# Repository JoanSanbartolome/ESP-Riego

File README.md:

# ESP-Riego

Controlador inalámbrico de riego por goteo basado en ESP32 e integrado en Home Assistant mediante ESPHome.

Este repositorio contiene el rediseño (v2) de la PCB desarrollada en el Trabajo Fin de Grado de Joan San Bartolomé Ferri. El proyecto original del TFG no se modifica: se importa como referencia y la v2 se diseña desde cero a partir de su análisis.

## Estado

| Fase | Estado |
|---|---|
| 0. Análisis, especificaciones y plan | ✅ |
| 1. Importación de la v1 a KiCad 10 | ⏳ |
| 2. Arquitectura y componentes | — |
| 3. Esquema v2 | — |
| 4. Layout v2 | — |
| 5. Fabricación | — |
| 6. Firmware y validación | — |

## Documentación

1. [Análisis de la PCB v1](docs/01-analisis-v1.md): estado de la placa del TFG y hallazgos.
2. [Especificaciones de la PCB v2](docs/02-especificaciones-v2.md): requisitos, criterios de aceptación y decisiones abiertas.
3. [Plan de diseño](docs/03-plan-de-diseno.md): fases e hitos.
4. [Sistema de gestión](gestion/README.md): roles, ciclo de vida de las specs, commits y auditoría. Estado actual en el [tablero](gestion/TABLERO.md) y en la [trazabilidad de requisitos](gestion/TRAZABILIDAD.md).

## Organización del trabajo

El diseño lo hacen agentes de Claude Code coordinados por la sesión principal ([DEC-0001](gestion/decisiones/DEC-0001-orquestacion-de-agentes.md) y [DEC-0009](gestion/decisiones/DEC-0009-orquestacion-v2.md)):

| Agente | Responsable de |
|---|---|
| Coordinador | Specs, órdenes, git, tablero y comunicación |
| `ing-diseno` | Cada bloque de principio a fin: cálculos, piezas, esquema y PCB |
| `jr-conformidad` | Tipo y stock, fichas, campos, BOM, CPL y paquetes de fabricación |
| `ing-validacion` | Revisión contra especificaciones e informes con veredicto |

Cada unidad de trabajo es una spec (un bloque o un hito de layout) con su propia rama, validada antes de integrarse en `main`. Lo que toca ahora está en [`gestion/ESTADO.md`](gestion/ESTADO.md).

## Estructura

```
.
├── docs/            Análisis, especificaciones, plan, cálculos y planes de prueba
├── hardware/
│   ├── libraries/   Símbolos, huellas y modelos 3D propios (rutas ${KIPRJMOD})
│   ├── componentes/ Fichas de componentes
│   ├── v1-tfg/      Proyecto del TFG migrado a KiCad 10
│   └── v2/          Nuevo diseño
├── firmware/        Configuración ESPHome
├── fabricacion/     Salidas de fabricación por versión
├── gestion/         Specs, logs, informes, decisiones, checklists y plantillas
├── herramientas/    Scripts de gestión y verificación
├── .claude/         Agentes, hooks y memoria de los agentes
└── .githooks/       Validación de los mensajes de commit
```

Las carpetas de diseño se crean a medida que avanzan las fases.

## Requisitos

- [KiCad 10](https://www.kicad.org/)
- Python 3 (scripts de `herramientas/` y hooks)
- [ESPHome](https://esphome.io/) para el firmware

Al clonar el repositorio, activa la validación de commits:

```bash
git config core.hooksPath .githooks
```

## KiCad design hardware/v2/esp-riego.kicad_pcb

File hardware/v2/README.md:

# v2 — ESP-Riego (esqueleto de trabajo)

Proyecto KiCad 10 `esp-riego`. Nació como copia de la v1 (`hardware/v1-tfg/`, etiqueta `v1.1-tfg`, SPEC-0013) y en SPEC-0014 se vació: se retiraron todos los circuitos de la v1 que no encajan en los requisitos v0.4 (`docs/02-especificaciones-v2.md`, DEC-0002, DEC-0003 y DEC-0004). El inventario de lo retirado está en `gestion/logs/SPEC-0014/01-ing-esquematicos.md`.

Cajetín: hoja de dibujo `../libraries/ESP-Riego.kicad_wks`, título «ESP-Riego v2», revisión 2.0-dev. `comment 1` lleva la descripción de cada hoja («Placa de control de riego» en la raíz).

## Hojas

| Hoja (`Sheetname` · archivo) | Bloque pendiente | Requisitos | Contenido actual |
|---|---|---|---|
| `Alimentacion` · `alimentacion.kicad_sch` (A3) | Entrada, protecciones, limitador común, buck, 3,3 V | ALI-01 … ALI-13 | **Bloque de la v2** (SPEC-0019): J1, F1, Q1, D1–D4, U1–U4, L1, JP1, TP1–TP5 y pasivos, según `docs/diseno/alimentacion.md`. Pines de hoja: `BUS_24V`, `VIN_SENSE`, `LIM_IMON`, `LIM_FLT`, `LIM_EN` y `VBUS` |
| `MCU` · `mcu.kicad_sch` (A3) | ESP32-S3-WROOM-1, USB-C, BOOT/RESET, UART | MCU-01 … MCU-07, FW-02 | **Bloque de la v2** (SPEC-0022): U5, U6, J2, J3, SW1, SW2, D5 y pasivos, según `docs/diseno/mcu.md`. 25 pines de hoja (Anexo C de `mcu.md`) |
| `Salidas` · `salidas.kicad_sch` | 6 *high-side* BTT6050 con diagnóstico y sus bornes | REL-01 … REL-10 | Texto del bloque pendiente |
| `Sensores` · `sensores.kicad_sch` | Temperatura y humedad del aire de la caseta | AMB-01, AMB-02 | **Bloque de la v2** (SPEC-0029): U13 SHT40-AD1B (I²C 0x44) y C47, según `docs/diseno/sensores.md`. Pines de hoja: `I2C_SDA` e `I2C_SCL`, unidos a la hoja MCU (R24/R25 en MCU) |
| `Conectores` · `conectores.kicad_sch` | Entrada de pulsos, expansión, reparto de bornes | EXP-01 … EXP-04, FAB-07, FAB-08 | Texto del bloque pendiente y H1–H4 (taladros M3, FAB-08) |

Cada bloque crea sus pines jerárquicos. En la raíz, `VBUS`, `VIN_SENSE`, `LIM_IMON`, `LIM_FLT` y `LIM_EN` unen MCU y Alimentacion con etiquetas locales (SPEC-0022), e `I2C_SDA`/`I2C_SCL` unen MCU y Sensores (SPEC-0029). Los pines sin hoja de destino llevan una marca de no conexión **provisional** (desde SPEC-0029, solo `I2C_EXP_SDA`, `I2C_EXP_SCL`, `EXP_INT`, `EXP_IO2` y `PULSE_IN` de MCU): la spec de Conectores la quita. +5V, +3V3 y GND son símbolos de alimentación globales.

## Puente JP1 del limitador (DEC-0006)

JP1 es un puente de soldadura de `VIN_PROT` a `BUS_24V`, en paralelo con U1 (TPS26632). **Va abierto**, con U1 montado. Solo se cierra, con una gota de estaño, si U1 no se monta o falla abierto. Con U1 sano no se cierra: la corriente se lo saltaría. Serigrafía: «JP1: abierto = limitador · cerrado = sin limitador».

Con JP1 cerrado (y sin U1) se pierde (`docs/diseno/alimentacion.md` §3.13.9):

- la limitación común a 3,86–4,57 A (ALI-13): un corto en una salida lo limitan la fuente (≥ 5,14 A) y el BTT6050 (≥ 38 A); `VIN_PROT` cae y la lógica puede reiniciarse, así que **REL-08 no se cumple**;
- el corte general del bus por `LIM_EN`: el bus queda siempre alimentado;
- `LIM_FLT` e `LIM_IMON`: FLT lee alto siempre e IMON 0 V; en el firmware hay que activar la opción «sin limitador»;
- el *clamp* del bus a ≤ 35 V: el bus ve `VIN_PROT` hasta 53,3 V, dentro de los 65 V del BTT6050;
- el arranque suave del bus (dVdT).

Se mantiene REL-04: cada IN de las salidas tiene su *pull-down*, así que las salidas siguen apagadas en el reset y el flasheo. Los pads tienen conexión sólida a la zona: para cerrarlo hace falta un soldador potente o punta ancha.

## PCB

Sincronizada con el esquema, sin colocar ni rutar (SPEC-0019 y SPEC-0022; detalle en `gestion/logs/SPEC-0022/02-ing-layout.md`). Tiene 80 huellas: H1–H4 dentro del contorno, y fuera de él, agrupadas por posición, las 55 de Alimentacion (x 10–92, y 60–113 mm) y las 21 de la hoja MCU (x 10–64, y 120–198 mm). Sin pistas, vías ni zonas.

- Contorno **preliminar** de 100 × 70 mm en `Edge.Cuts` (FAB-08), de (100, 60) a (200, 130) mm; el origen auxiliar y el de la rejilla están en la esquina inferior izquierda. Un texto en `User.Comments` lo marca como preliminar hasta el *floorplan*.
- H1–H4 (`MountingHole_3.2mm_M3_Pad_Via`, anillo sin red), a 4 mm de los dos bordes de su esquina: H3 arriba a la izquierda, H1 arriba a la derecha, H4 abajo a la izquierda y H2 abajo a la derecha.
- Reglas de FAB-02 en el `.kicad_pro`: pista y separación ≥ 0,2 mm, vía 0,6/0,3 mm, cobre a borde ≥ 0,5 mm. Solo existe la clase `Default` (0,2 mm, vía 0,6/0,3). Las clases de FAB-03 y el `.kicad_dru` (KIC-04) llegan con el layout.
- `pcbplotparams/outputdirectory` vacío y sin `embedded_files`.

## Cómo se trabaja

Cada bloque llega con su propia spec. La PCB se actualiza desde el esquema en cada bloque; el layout definitivo se hace cuando el esquema esté estable.

Las librerías están en `../libraries/` (tablas con `${KIPRJMOD}/../libraries/...`). Desde SPEC-0019 las tablas del proyecto solo tienen `esp-riego` (símbolos y huellas propios de la v2); el resto son las oficiales de KiCad 10. Las librerías de la v1 siguen en `../libraries/` para `v1-tfg`, que tiene sus propias tablas (VAL-0014-01-02).

Verificación: `python herramientas/verificar.py hardware/v2`. Estado tras el paso 2 de SPEC-0022: ERC 0 (0 avisos), DRC 0 (0 avisos; 172 sin conectar porque la PCB no está rutada) y paridad 0. Las 21 huellas de la hoja MCU están fuera del contorno hasta la spec de colocación.

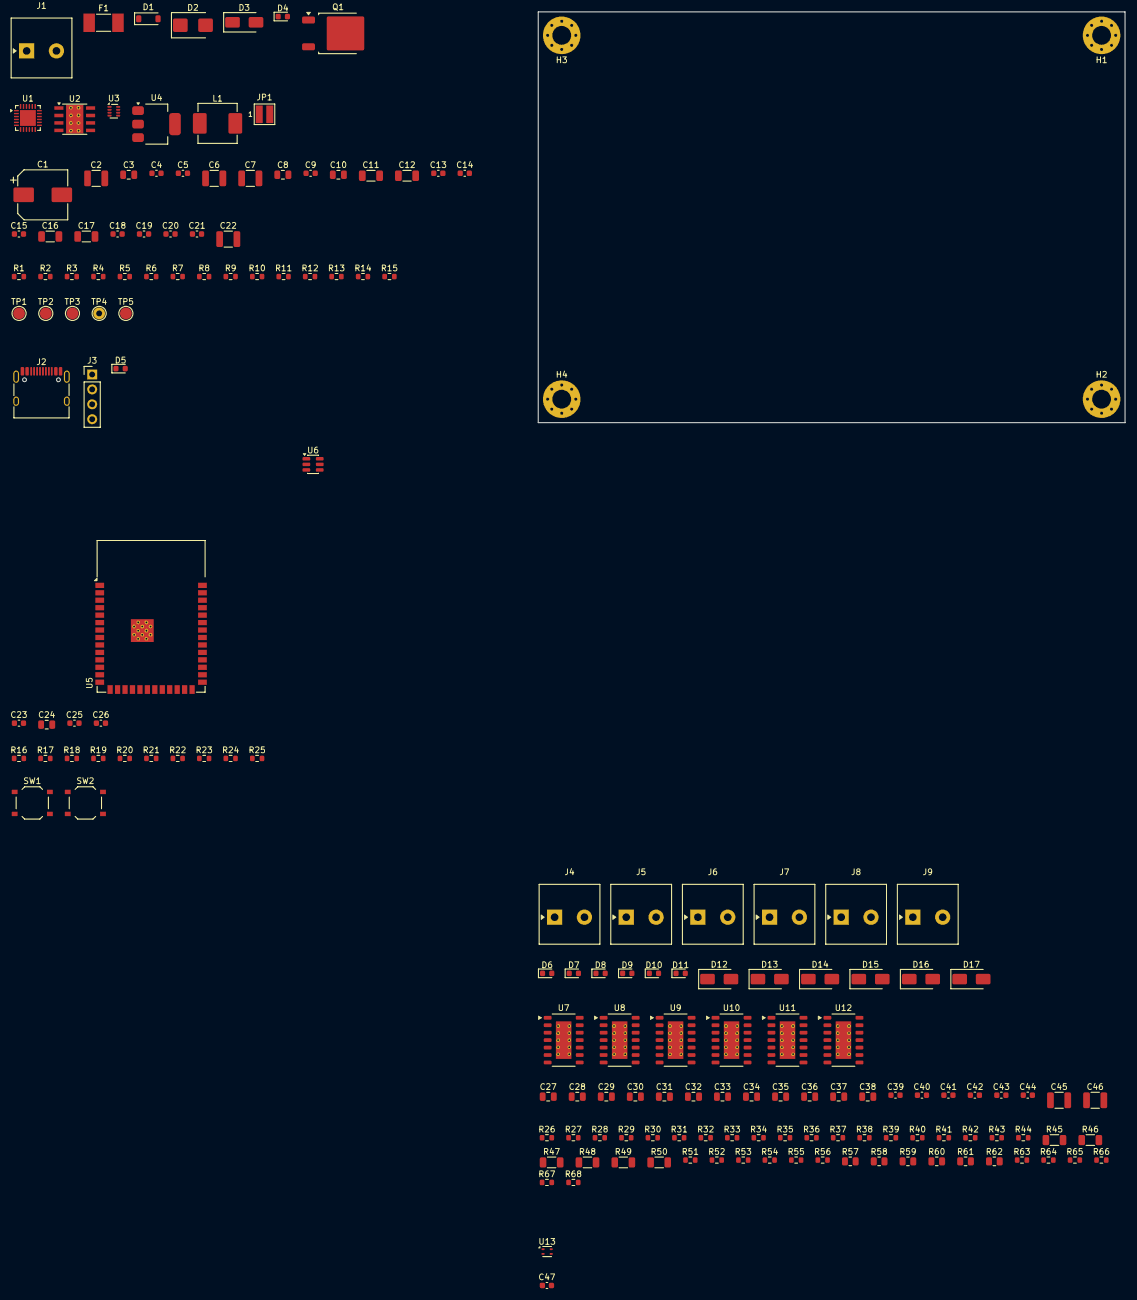
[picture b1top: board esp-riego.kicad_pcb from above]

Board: 2 copper layers, 100.0 x 70.0 mm, 169 parts (0 on the bottom side), 82 nets, no tracks yet.

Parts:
C1: 47u 63V; CP_Elec_8x10
C2, C6, C7, C22, C45, C46: 4.7u 100V; C_1210_3225Metric
C3, C8, C27, C28, C29, C30, C31, C32, C33, C34, C35, C36, C37, C38: 220n 100V; C_0805_2012Metric
C4: 22n; C_0603_1608Metric
C5, C9, C13, C14, C20, C21, C39, C40, C41, C42, C43, C44, C47: 100n; C_0603_1608Metric
C10: 1u 50V; C_0805_2012Metric
C11, C12, C16, C17: 22u 25V; C_1206_3216Metric
C15: 1u; C_0603_1608Metric
C18, C19: 10u; C_0603_1608Metric
C23: 1uF; C_0603_1608Metric
C24: 22uF; C_0805_2012Metric
C25: 100nF; C_0603_1608Metric
C26: 4.7uF; C_0603_1608Metric
D1: BZT52C15; D_SOD-123
D2: SMBJ33A; D_SMB
D3: SS310; D_SMA
D4, D6, D7, D8, D9, D10, D11: Rojo; LED_0603_1608Metric
D5: LED; LED_0603_1608Metric
D12, D13, D14, D15, D16, D17: M7; D_SMA
F1: 10A; Fuse_Littelfuse-NANO2-451_453
H1, H2, H3, H4: MountingHole; MountingHole_3.2mm_M3_Pad_Via
J1, J4, J5, J6, J7, J8, J9: WJ500V-5.08-2P; TerminalBlock_Kangnex_WJ500V-5.08-2P_1x02_P5.08mm_Horizontal
J2: USB_C_Receptacle_USB2.0_16P; USB_C_Receptacle_HRO_TYPE-C-31-M-12
J3: Conn_01x04; PinHeader_1x04_P2.54mm_Vertical
JP1: Puente U1; SolderJumper-2_P1.8mm_Open_Pad1.2x3.0mm
L1: 10u; L_Changjiang_FXL0650
Q1: SQD50P06-15L; TO-252-2
R1, R9, R12, R32, R33, R34, R35, R36, R37, R44: 100k; R_0603_1608Metric
R2: 4.3k; R_0603_1608Metric
R3, R4, R5, R6, R10, R16, R17, R26, R27, R28, R29, R30, R31, R38, R39, R40, R41, R42, R43: 10k; R_0603_1608Metric
R7, R14: 100k 0.1%; R_0603_1608Metric
R8: 24.9k 0.1%; R_0603_1608Metric
R11: 330k; R_0603_1608Metric
R13, R23, R63, R64, R65, R66, R67, R68: 1k; R_0603_1608Metric
R15: 4.87k 0.1%; R_0603_1608Metric
R18, R19: 5k1; R_0603_1608Metric
R20, R21: 22; R_0603_1608Metric
R22: 470; R_0603_1608Metric
R24, R25: 4k7; R_0603_1608Metric
R45, R46, R47, R48, R49, R50: 10k; R_1206_3216Metric
R51, R52, R53, R54, R55, R56: 820; R_0603_1608Metric
R57, R58, R59, R60, R61, R62: 47k; R_0805_2012Metric
SW1, SW2: SW_Push; SW_Push_1P1T_XKB_TS-1187A
TP1: VIN_PROT; TestPoint_Pad_D2.0mm
TP2: +5V; TestPoint_Pad_D2.0mm
TP3: +3V3; TestPoint_Pad_D2.0mm
TP4: GND; TestPoint_THTPad_D2.0mm_Drill1.0mm
TP5: BUS_24V; TestPoint_Pad_D2.0mm
U1: TPS26632RGER; Texas_RGE0024H_VQFN-24-1EP_4x4mm_P0.5mm_EP2.7x2.7mm
U2: LMR36520FADDAR; Texas_DDA0008B_HTSOP-8-1EP_3.9x4.9mm_P1.27mm_EP2.95x4.9mm_M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
U3: TPS2116DRLR; SOT-583-8
U4: TLV1117LV33DCYR; SOT-223-3_TabPin2
U5: ESP32-S3-WROOM-1-N8; ESP32-S3-WROOM-1
U6: USBLC6-2SC6; SOT-23-6
U7, U8, U9, U10, U11, U12: BTT6050-1ERA; Infineon_PG-TDSO-14_8.65x3.9mm_P1.27mm_EP2.65x6.4mm
U13: SHT40-AD1B-R3; Sensirion_DFN-4_1.5x1.5mm_P0.8mm_SHT4x_NoCentralPad

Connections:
+3V3: C19.1, C21.1, C24.1, C25.1, C47.1, J3.1, R6.1, R13.1, R16.1, R17.1, R24.1, R25.1, TP3.1, U4.2, U5.2, U13.3
+5V: C16.1, C17.1, C18.1, TP2.1, U3.2, U3.7, U4.3
/Alimentacion/+5V_BUCK: C11.1, C12.1, C14.1, L1.2, R7.1, R11.1, U3.3, U3.5
/Alimentacion/EN_BUCK: C13.1, R9.2, R10.1, U2.3
/Alimentacion/Q1_G: D1.2, Q1.1, R1.1
/Alimentacion/U1_DVDT: C4.1, U1.9
/Alimentacion/U1_ILIM: R2.1, U1.10
/Alimentacion/U1_IMON: R3.1, R4.1, U1.13
/Alimentacion/U2_BOOT: C9.1, U2.7
/Alimentacion/U2_FB: R7.2, R8.1, U2.5
/Alimentacion/U2_SW: C9.2, L1.1, U2.8
/Alimentacion/U2_VCC: C10.1, U2.6
/Alimentacion/U3_PR1: R11.2, R12.1, U3.4
/Alimentacion/VIN_F: F1.2, Q1.2
/Alimentacion/VIN_PROT: C1.1, C2.1, C3.1, C7.1, C8.1, C22.1, D1.1, D2.1, JP1.1, Q1.3, R9.1, R14.1, TP1.1, U1.1, U1.2, U1.5, U2.2
/Alimentacion/VIN_RAW: F1.1, J1.1
/BUS_24V: C6.1, C27.1, C28.1, C29.1, C30.1, C31.1, C32.1, C45.1, C46.1, D3.1, JP1.2, R57.1, R58.1, R59.1, R60.1, R61.1, R62.1, TP5.1, U1.17, U1.18, U7.15, U8.15, U9.15, U10.15, U11.15, U12.15
/I2C_SCL: R25.2, U5.35, U13.2
/I2C_SDA: R24.2, U5.34, U13.1
/IN1: R26.1, R32.1, R63.1, U5.19
/IN2: R27.1, R33.1, R64.1, U5.20
/IN3: R28.1, R34.1, R65.1, U5.21
/IN4: R29.1, R35.1, R66.1, U5.8
/IN5: R30.1, R36.1, R67.1, U5.9
/IN6: R31.1, R37.1, R68.1, U5.10
/IS1: C39.1, R45.2, R51.1, U5.4
/IS2: C40.1, R46.2, R52.1, U5.5
/IS3: C41.1, R47.2, R53.1, U5.6
/IS4: C42.1, R48.2, R54.1, U5.7
/IS5: C43.1, R49.2, R55.1, U5.12
/IS6: C44.1, R50.2, R56.1, U5.17
/LIM_EN: R5.1, U1.12, U5.23
/LIM_FLT: R6.2, U1.14, U5.22
/LIM_IMON: C5.1, R4.2, U5.38
/MCU/BOOT: R17.2, SW2.1, U5.27
/MCU/CC1: J2.A5, R18.1
/MCU/CC2: J2.B5, R19.1
/MCU/EN: C23.1, R16.2, SW1.1, U5.3
/MCU/LED_A: D5.2, R23.2
/MCU/LED_STATUS: R23.1, U5.33
/MCU/TXD0: R22.1, U5.37
/MCU/UART_RX: J3.3, U5.36
/MCU/UART_TX: J3.2, R22.2
/MCU/USB_DM: R21.2, U5.13
/MCU/USB_DM_C: J2.A7, J2.B7, R21.1, U6.3, U6.4
/MCU/USB_DP: R20.2, U5.14
/MCU/USB_DP_C: J2.A6, J2.B6, R20.1, U6.1, U6.6
/OUT_DEN: R38.1, R39.1, R40.1, R41.1, R42.1, R43.1, R44.1, U5.31
/Salidas/DEN1_HS: R38.2, U7.5
/Salidas/DEN2_HS: R39.2, U8.5
/Salidas/DEN3_HS: R40.2, U9.5
/Salidas/DEN4_HS: R41.2, U10.5
/Salidas/DEN5_HS: R42.2, U11.5
/Salidas/DEN6_HS: R43.2, U12.5
/Salidas/IN1_HS: R26.2, U7.4
/Salidas/IN2_HS: R27.2, U8.4
/Salidas/IN3_HS: R28.2, U9.4
/Salidas/IN4_HS: R29.2, U10.4
/Salidas/IN5_HS: R30.2, U11.4
/Salidas/IN6_HS: R31.2, U12.4
/Salidas/IS1_HS: R45.1, U7.6
/Salidas/IS2_HS: R46.1, U8.6
/Salidas/IS3_HS: R47.1, U9.6
/Salidas/IS4_HS: R48.1, U10.6
/Salidas/IS5_HS: R49.1, U11.6
/Salidas/IS6_HS: R50.1, U12.6
/Salidas/LED1_A: D6.2, R63.2
/Salidas/LED2_A: D7.2, R64.2
/Salidas/LED3_A: D8.2, R65.2
/Salidas/LED4_A: D9.2, R66.2
/Salidas/LED5_A: D10.2, R67.2
/Salidas/LED6_A: D11.2, R68.2
/Salidas/OUT1: C33.1, D12.1, J4.1, R57.2, U7.10, U7.11, U7.12
/Salidas/OUT2: C34.1, D13.1, J5.1, R58.2, U8.10, U8.11, U8.12
/Salidas/OUT3: C35.1, D14.1, J6.1, R59.2, U9.10, U9.11, U9.12
/Salidas/OUT4: C36.1, D15.1, J7.1, R60.2, U10.10, U10.11, U10.12
/Salidas/OUT5: C37.1, D16.1, J8.1, R61.2, U11.10, U11.11, U11.12
/Salidas/OUT6: C38.1, D17.1, J9.1, R62.2, U12.10, U12.11, U12.12
/VBUS: C15.1, C26.1, J2.A4, J2.A9, J2.B4, J2.B9, U3.6, U6.5
/VIN_SENSE: C20.1, R14.2, R15.1, U5.39
GND: C1.2, C2.2, C3.2, C4.2, C5.2, C6.2, C7.2, C8.2, C10.2, C11.2, C12.2, C13.2, C14.2, C15.2, C16.2, C17.2, C18.2, C19.2, C20.2, C21.2, C22.2, C23.2, C24.2, C25.2, C26.2, C27.2, C28.2, C29.2, C30.2, C31.2, C32.2, C33.2, C34.2, C35.2, C36.2, C37.2, C38.2, C39.2, C40.2, C41.2, C42.2, C43.2, C44.2, C45.2, C46.2, C47.2, D2.2, D3.2, D4.1, D5.1, D6.1, D7.1, D8.1, D9.1, D10.1, D11.1, D12.2, D13.2, D14.2, D15.2, D16.2, D17.2, J1.2, J2.A1, J2.A12, J2.B1, J2.B12, J2.SH, J3.4, J4.2, J5.2, J6.2, J7.2, J8.2, J9.2, R1.2, R2.2, R3.2, R5.2, R8.2, R10.2, R12.2, R15.2, R18.2, R19.2, R32.2, R33.2, R34.2, R35.2, R36.2, R37.2, R44.2, R51.2, R52.2, R53.2, R54.2, R55.2, R56.2, SW1.2, SW2.2, TP4.1, U1.6, U1.7, U1.8, U1.15, U1.25, U2.1, U2.9, U3.1, U4.1, U5.1, U5.40, U5.41, U6.2, U7.3, U8.3, U9.3, U10.3, U11.3, U12.3, U13.4
unnamed: D4.2, R13.2

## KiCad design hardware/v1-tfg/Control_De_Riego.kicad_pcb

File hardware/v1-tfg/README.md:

# v1-tfg — proyecto del TFG en formato KiCad 10

Copia de la v1 (`Control_De_Riego`) del TFG de Joan San Bartolomé Ferri. **El diseño no se ha tocado**: solo se han cambiado las rutas de librería, la hoja de dibujo, los modelos 3D y el formato de archivo (SPEC-0009). Los hallazgos H1–H12 de `docs/01-analisis-v1.md` siguen presentes.

## Origen

`C:\Users\josan\proyectos\TFG\KiCad_PCB\Control_De_Riego` (carpeta de trabajo, igual que `PCB_FINAL.rar`) y `C:\Users\josan\proyectos\TFG\Llibreries_Kicad`. Solo se leyó del TFG; su huella (`gestion/tfg-manifiesto.json`) sigue intacta.

## Qué se copió

- Proyecto: `Control_De_Riego.kicad_pro`, `.kicad_sch` (raíz), `allimentacion`, `conectores`, `modulo_reles`, `wemos_s2mini` (`.kicad_sch`) y `Control_De_Riego.kicad_pcb`.
- `referencia/Panel_Control.kicad_sch`: hoja fuera de la jerarquía (H9), solo como referencia. Está guardada también en formato KiCad 10.
- Librerías propias en `../libraries/` con los mismos nicknames que las tablas originales (ver abajo).

No se copió: `Control_De_Riego-backups/`, `fp-info-cache`, `.kicad_prl`, `.step` del proyecto, `untitled.kicad_sch` (duplicado del Wemos) ni los `.rar`.

## Librerías (`../libraries/`)

| Nickname | Tipo | Archivo | Origen |
|---|---|---|---|
| `PS2705-1-F3-A`, `BC817-25-7-F`, `1548129`, `PRT-10811` | símbolos | `<nick>.kicad_sym` | `.lib` + `.dcm` de la librería del TFG, convertidos con `kicad-cli sym upgrade` |
| `Wemos s2 mini` | símbolo | `Wemos s2 mini.kicad_sym` | JSON de EasyEDA (`SCHLIB_WEMOS-S2-MINI-…json`) convertido tal cual con `kicad-cli sym upgrade -o` (SPEC-0010) |
| `PS2705`, `BC817-25-7`, `PRT10811`, `KiCad`, `PhoenixTerminal`, `SMMS0530-150M` | huellas | `<nick>.pretty` | `.kicad_mod` de la librería del TFG, actualizados con `kicad-cli fp upgrade` (`KiCad` = `1548129`; `SMMS0530-150M` incluye también `IND-SMD_L5.5-W5.2`) |
| `Wemos s2 mini` | huella | `Wemos s2 mini.pretty` | JSON de EasyEDA (`PCBLIB_WEMOS-S2-MINI_…json`) convertido tal cual con `kicad-cli fp upgrade -o` (SPEC-0010); no lleva modelo 3D |
| `DC-Jack` | huella | `DC-Jack.pretty/DC-IN-TH_XDJK-0051-025` | JSON de EasyEDA convertido tal cual con `kicad-cli fp upgrade -o` (SPEC-0010). Tiene 3 pads; el pad 3 es `custom` con polígono de 3,56 × 1,60 mm y taladro oblongo de 3×1 mm, equivalente a los pads 1 y 2 girados 90° (no es un artefacto). No se usa en la PCB (el jack real es `Connector_BarrelJack`) |

También `Cajetin_Kicad.kicad_wks` (hoja de dibujo) y `3d/` (`TLP185.step`, `Transistor.IGS`, `PSMT3012.STEP`, `Wemos S2 Mini V1.0.0.step`).

## Cambios de ruta

- `sym-lib-table` y `fp-lib-table`: reescritas con `${KIPRJMOD}/../libraries/...` y tipo `KiCad` (antes `Legacy` y EasyEDA, con rutas `G:/…`).
- `Control_De_Riego.kicad_pro`: `page_layout_descr_file` (dos apariciones) a `${KIPRJMOD}/../libraries/Cajetin_Kicad.kicad_wks`; `export… svg` (ruta `C:/Users/josan/Desktop/…`, último directorio de exportación) vaciado.
- `Control_De_Riego.kicad_pcb`: 10 modelos 3D con ruta `G:/…` a `${KIPRJMOD}/../libraries/3d/<archivo>` (4× TLP185, 4× Transistor, 1× PSMT3012, 1× Wemos); 43 modelos `${KICAD9_3DMODEL_DIR}` a `${KICAD10_3DMODEL_DIR}` (normalización a la variable de KiCad 10; la antigua también resuelve, así que el cambio es inocuo).
- Modelos 3D: 42 de los 53 modelos de la PCB apuntan a un `.wrl`, y KiCad 10.0.6 no instala ningún `.wrl` (solo `.step`), así que esos modelos no se ven en el visor 3D ni en el STEP (`Could not add 3D model`). Viene de la v1; se corrige en la copia de trabajo de la v2 (`.wrl` a `.step`).
- Esquemas y PCB: `kicad-cli sch|pcb upgrade --force` (esquema `20260306`, PCB `20260206`).

## Verificación

`python herramientas/verificar.py hardware/v1-tfg`:

| | Antes (copia sin migrar) | Después |
|---|---|---|
| ERC | 1 (`pin_to_pin`) | 1 (`pin_to_pin`) |
| DRC | 1 error `starved_thermal`, 39 `lib_footprint_mismatch`, 0 sin conectar | 1 error `starved_thermal`, 39 `lib_footprint_mismatch`, 0 sin conectar (40 en total, como antes) |
| Paridad | 77 (61 `LCSC Part#`, 10 `net_conflict`, 6 huellas) | 77 (igual) |

Tras SPEC-0010 el DRC coincide con la copia sin migrar: la huella `Wemos s2 mini` de la librería es la conversión del JSON de EasyEDA, igual que en el TFG, y vuelve a no coincidir con la copia de U1 en la PCB (`lib_footprint_mismatch`). Con la copia embebida en la PCB (SPEC-0009) el DRC era 39. Netlist (61 componentes, 70 redes), posiciones, pistas (262), vías (36) y zonas (3) son idénticas antes y después. Detalle en `gestion/logs/SPEC-0009/01-jr-conformidad.md`.

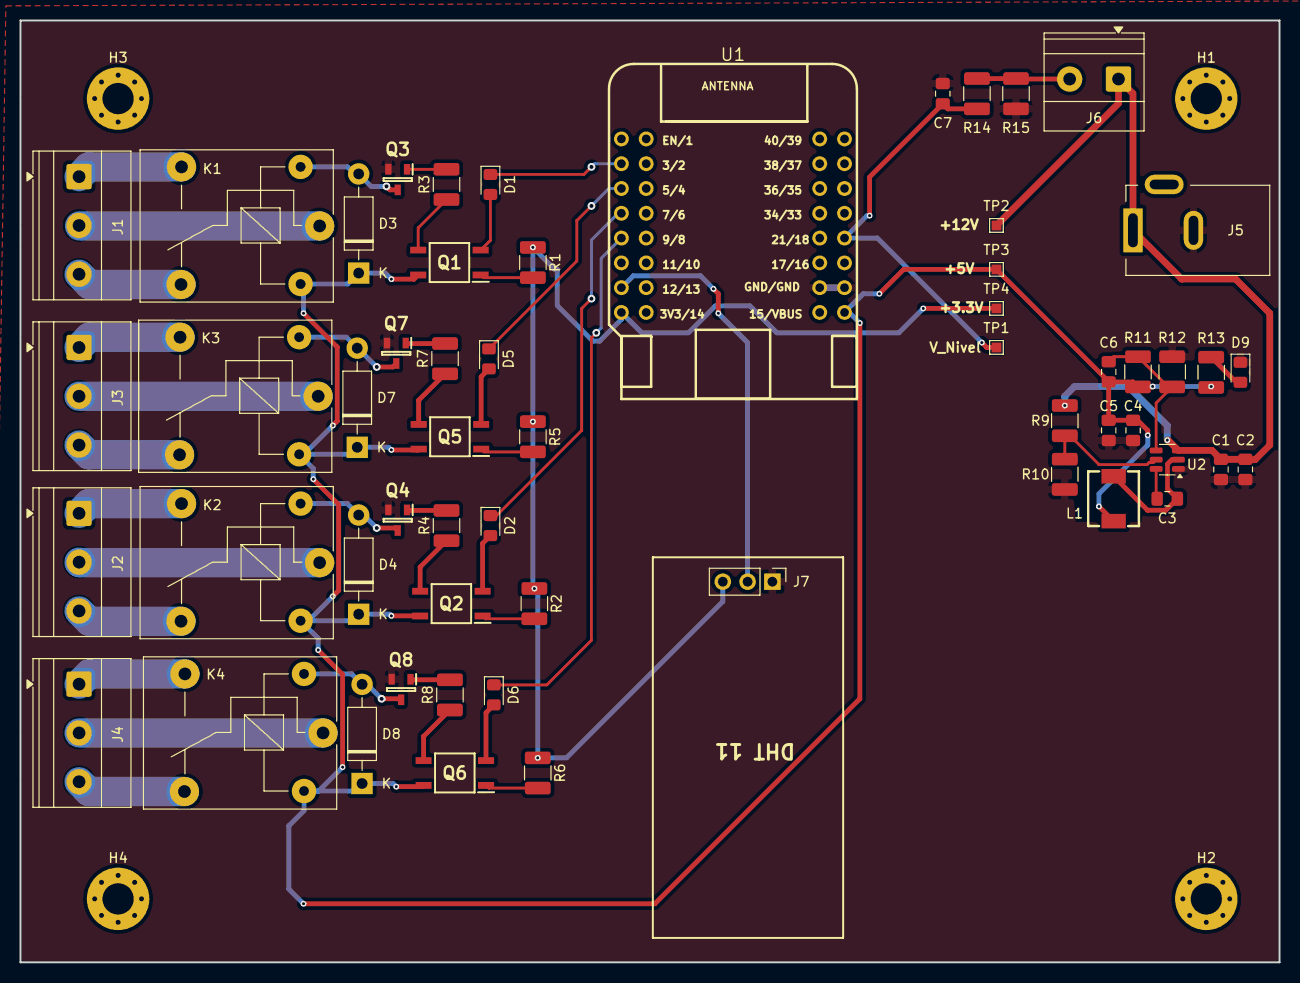
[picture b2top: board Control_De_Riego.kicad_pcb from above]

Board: 2 copper layers, 129.0 x 96.5 mm, 61 parts (0 on the bottom side), 48 nets.

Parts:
C1: 10uF; C_0805_2012Metric_Pad1.18x1.45mm_HandSolder
C2, C3, C7: 100nF; C_0805_2012Metric_Pad1.18x1.45mm_HandSolder
C4, C5: 22uF; C_0805_2012Metric_Pad1.18x1.45mm_HandSolder
C6: 68pF; C_0805_2012Metric_Pad1.18x1.45mm_HandSolder
D1, D2, D5, D6: Red; LED_0805_2012Metric_Pad1.15x1.40mm_HandSolder
D3, D4, D7, D8: 1N4007; D_DO-41_SOD81_P10.16mm_Horizontal
D9: Green; LED_0805_2012Metric_Pad1.15x1.40mm_HandSolder
H1, H2, H3, H4: MountingHole; MountingHole_3.2mm_M3_Pad_Via
J1: Conector Rele 1; TerminalBlock_Phoenix_MKDS-1,5-3_1x03_P5.00mm_Horizontal
J2: Conector Rele 3; TerminalBlock_Phoenix_MKDS-1,5-3_1x03_P5.00mm_Horizontal
J3: Conector Rele 2; TerminalBlock_Phoenix_MKDS-1,5-3_1x03_P5.00mm_Horizontal
J4: Conector Rele 4; TerminalBlock_Phoenix_MKDS-1,5-3_1x03_P5.00mm_Horizontal
J5: DC Jack; BarrelJack_Kycon_KLDX-0202-xC_Horizontal
J6: Conn_01x02; TerminalBlock_Phoenix_MKDS-1,5-2_1x02_P5.00mm_Horizontal
J7: Conn_01x03; PinHeader_1x03_P2.54mm_Vertical
K1, K2, K3, K4: SANYOU_SRD_Form_C; Relay_SPDT_SANYOU_SRD_Series_Form_C
L1: 22uH; IND-SMD_L5.5-W5.2
Q1, Q2, Q5, Q6: PS2705-1-F3-A; SOP254P700X230-4N
Q3, Q4, Q7, Q8: BC817-25-7-F; SOT96P240X110-3N
R1, R2, R5, R6: 50; R_1210_3225Metric_Pad1.30x2.65mm_HandSolder
R3, R4, R7, R8: 1k; R_1210_3225Metric_Pad1.30x2.65mm_HandSolder
R9, R14: 270k; R_1210_3225Metric_Pad1.30x2.65mm_HandSolder
R10: 33k; R_1210_3225Metric_Pad1.30x2.65mm_HandSolder
R11: 100k; R_1210_3225Metric_Pad1.30x2.65mm_HandSolder
R12: 13k; R_1210_3225Metric_Pad1.30x2.65mm_HandSolder
R13: 180; R_1210_3225Metric_Pad1.30x2.65mm_HandSolder
R15: 150; R_1210_3225Metric_Pad1.30x2.65mm_HandSolder
TP1, TP2, TP3, TP4: TestPoint; TestPoint_Pad_1.0x1.0mm
U1: WEMOS-S2-MINI (ESP32-S2FN4R2); WEMOS-S2-MINI
U2: TPS54202DDC; SOT-23-6

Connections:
+3.3V: J7.3, R1.1, R2.1, R5.1, R6.1, TP4.1, U1.15 (3V3)
+5V: C4.1, C5.1, C6.1, D3.1 (K), D4.1 (K), D7.1 (K), D8.1 (K), K1.5, K2.5, K3.5, K4.5, L1.2, Q1.4 (C), Q2.4 (C), Q5.4 (C), Q6.4 (C), R11.1, R13.1, TP3.1, U1.18 (VBUS)
+12V: C1.1, C2.1, J5.1, J6.1, R9.2, TP2.1, U2.3 (VIN)
/Modulo_reles/IN_REL1: J1.2, K1.1
/Modulo_reles/IN_REL2: J3.2, K3.1
/Modulo_reles/IN_REL3: J2.2, K2.1
/Modulo_reles/IN_REL4: J4.2, K4.1
/Modulo_reles/NC_REL1: J1.3, K1.4
/Modulo_reles/NC_REL2: J3.3, K3.4
/Modulo_reles/NC_REL3: J2.3, K2.4
/Modulo_reles/NC_REL4: J4.3, K4.4
/Modulo_reles/NO_REL1: J1.1, K1.3
/Modulo_reles/NO_REL2: J3.1, K3.3
/Modulo_reles/NO_REL3: J2.1, K2.3
/Modulo_reles/NO_REL4: J4.1, K4.3
GND: C1.2, C2.2, C4.2, C5.2, C7.2, D9.1 (K), J5.2, J7.1, Q3.2, Q4.2, Q7.2, Q8.2, R10.2, R12.1, R15.2, U1.19 (GND), U1.20 (GND), U2.1 (GND)
unnamed: D1.2 (A), Q1.2 (KA)
unnamed: D2.2 (A), Q2.2 (KA)
unnamed: D3.2 (A), K1.2, Q3.3
unnamed: D4.2 (A), K2.2, Q4.3
unnamed: D5.2 (A), Q5.2 (KA)
unnamed: D6.2 (A), Q6.2 (KA)
unnamed: D7.2 (A), K3.2, Q7.3
unnamed: D8.2 (A), K4.2, Q8.3
unnamed: D9.2 (A), R13.2
unnamed: J6.2, R14.2, R15.1
unnamed: Q1.1 (AK), R1.2
unnamed: Q1.3 (E), R3.1
unnamed: Q2.1 (AK), R2.2
unnamed: Q2.3 (E), R4.1
unnamed: Q3.1, R3.2
unnamed: Q4.1, R4.2
unnamed: Q5.1 (AK), R5.2
unnamed: Q5.3 (E), R7.1
unnamed: Q6.1 (AK), R6.2
unnamed: Q6.3 (E), R8.1
unnamed: Q7.1, R7.2
unnamed: Q8.1, R8.2
unnamed: C3.1, U2.6 (BOOT)
unnamed: R9.1, R10.1, U2.5 (EN)
unnamed: C6.2, R11.2, R12.2, U2.4 (FB)
unnamed: C3.2, L1.1, U2.2 (SW)
REL1: D1.1 (K), U1.3 (IO3)
REL2: D5.1 (K), U1.5 (IO5)
REL3: D2.1 (K), U1.7 (IO7)
REL4: D6.1 (K), U1.9 (IO9)
TH_Data: J7.2, U1.13 (IO12)
V_Level: C7.1, R14.1, TP1.1, U1.24 (IO18)
